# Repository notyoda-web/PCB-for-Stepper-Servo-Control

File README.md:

# STM32 Black Pill Stepper & Servo Control Board - Pin Mapping & Connections

This document details the exact pin-to-pin net connections and interface routing between the STM32 Black Pill microcontroller, the power subsystems, the A4988 stepper drivers, the servo headers, and communication peripherals, as established in the KiCad schematic .

---

## Power Input & Regulation Subsystem

* **J1 (XT60PW-M Power Input):**
  * Pin `P` (Positive / 12V rail): Connects directly to the main 3S LiPo battery input line, feeding the input terminals of both buck converters (`12V`) and the VMOT pins of A4988 drivers `A1` and `A2`.
  * Pin `N` (Negative / GND): Connects to the system common ground (`GND`).
* **3.3V Buck Converter:**
  * Input: Connected to `12V` rail from J1.
  * Output: Connected to the `3.3V` net, providing power to the Black Pill `VDD`/`3.3V` pins and auxiliary logic. Bulk smoothing capacitor `C1` is placed across the output.
* **5V Buck Converter:**
  * Input: Connected to `12V` rail from J1.
  * Output: Connected to the `5V` net, supplying power to the four hobby servo motor headers (`N1`, `N2`, `N5`, `N6`). Bulk smoothing capacitor `C2` is placed across the output.

---

# Power Distribution & Decoupling Rationale

This document outlines the engineering reasons for using dual buck converters and four electrolytic capacitors in the STM32 Black Pill stepper and servo control board, as shown in the schematic and PCB layout.

---

## 1. The Use of Two Buck Converters

The board utilizes two separate step-down (buck) converters fed by the 3S LiPo battery (`12V` net) to establish distinct power domains:

* **Isolation of Inductive Noise:** Stepper motors and hobby servos generate massive voltage transients, back-EMF, and high-frequency current spikes on their power rails during switching and stalling. By separating the regulation paths, noisy high-power actuator rails are prevented from coupling directly into sensitive digital logic.
* **Dedicated Voltage Domains:** 
  * **5V Buck Converter:** Powers the four hobby servos (`N1`, `N2`, `N5`, `N6`), which draw heavy peak currents under load. Supplying them from a dedicated regulator prevents voltage sags from resetting the microcontroller.
  * **3.3V Buck Converter:** Supplies a clean, stable regulated voltage exclusively to the Black Pill microcontroller (`VDD`/`3.3V`), protecting its internal ADC, core logic, and communication peripherals from brownouts.

---

## 2. The Use of Four Electrolytic Capacitors (`C1`, `C2`, `C3`, `C4`)

The four bulk electrolytic capacitors serve specific filtering and energy-storage functions across the power architecture:

* **Regulator Output Smoothing (`C1` and `C2`):**
  * **`C1` (3.3V Rail):** Placed at the output of the 3.3V buck converter to filter out residual switching ripple, ensuring a steady, low-noise supply for the Black Pill.
  * **`C2` (5V Rail):** Positioned at the 5V regulator output to provide bulk charge reservoirs that instantly compensate for current surges when servos suddenly start moving or change direction.
* **Motor Driver Local Decoupling (`C3` and `C4`):**
  * **`C3` and `C4` (VMOT Decoupling):** Connected directly across the motor supply (`VMOT`) and ground (`GND`) of the two A4988 driver modules (`A1` and `A2`). 
  * **Transient Suppression:** Stepper drivers rapidly chop high currents through inductive windings, creating high-frequency voltage spikes that can destroy silicon. These bulk capacitors act as local energy buffers right next to the driver chips, absorbing back-EMF spikes and stabilizing the input voltage during rapid microstepping steps.

## Stepper Motor Subsystem (A4988 Drivers & Connectors)

* **Driver A1 (Left Stepper Driver):**
  * **Power & Decoupling:** `VMOT` connected to `12V` with electrolytic decoupling capacitor `C3` tied to `GND`; `VDD` connected to `3.3V`.
  * **Control Pins:** 
    * `STEP` $\rightarrow$ Connected to MCU pin `PA1`.
    * `DIR` $\rightarrow$ Connected to MCU pin `PA2`.
    * `ENABLE` $\rightarrow$ Connected to MCU pin `PA6`.
    * Microstepping (`MS1`, `MS2`, `MS3`) $\rightarrow$ Tied to MCU pins `pb2`, `pb1`, `pb0` respectively.
    * `SLEEP` & `RESET` $\rightarrow$ Tied together on the module.
  * **Motor Output (`N4`):**
    * Pins `1B`, `1A`, `2A`, `2B` mapped directly from A1 driver pins 3, 4, 5, 6 to motor connector `N4` (`1A1_181`, `1A`, `2A`, `2B`).

* **Driver A2 (Right Stepper Driver):**
  * **Power & Decoupling:** `VMOT` connected to `12V` with electrolytic decoupling capacitor `C4` tied to `GND`[cite: 3]; `VDD` connected to `3.3V`.
  * **Control Pins:**
    * `STEP` $\rightarrow$ Connected to MCU pin `PB15`.
    * `DIR` $\rightarrow$ Connected to MCU pin `PB14`.
    * `ENABLE` $\rightarrow$ Connected to MCU pin `PB5`.
    * Microstepping (`MS1`, `MS2`, `MS3`) $\rightarrow$ Tied to MCU pins `pb14` (shared/routed), `pb13`, `pb12`.
    * `SLEEP` & `RESET` $\rightarrow$ Tied together on the module.
  * **Motor Output (`N3`):**
    * Pins `1B`, `1A`, `2A`, `2B` mapped directly from A2 driver pins to motor connector `N3`.

---

## Servo Motor Subsystem

All four servo headers share a common power (`5V`) and ground (`GND`) bus, with individual PWM control lines driven directly by MCU GPIO/timer pins:

* **Servo Header N2:** Pin 1 (Signal) $\rightarrow$ MCU pin `PB6`; Pin 2 $\rightarrow$ `5V`; Pin 3 $\rightarrow$ `GND`.
* **Servo Header N1:** Pin 1 (Signal) $\rightarrow$ MCU pin `PB7`; Pin 2 $\rightarrow$ `5V`; Pin 3 $\rightarrow$ `GND`.
* **Servo Header N6:** Pin 1 (Signal) $\rightarrow$ MCU pin `PB8`; Pin 2 $\rightarrow$ `5V`; Pin 3 $\rightarrow$ `GND`.
* **Servo Header N5:** Pin 1 (Signal) $\rightarrow$ MCU pin `PB9`; Pin 2 $\rightarrow$ `5V`; Pin 3 $\rightarrow$ `GND`.

---

## Communication Interface (UART)

* **J3 (UART Header):**
  * Pin 1 (`Rx`) $\rightarrow$ Connected to Black Pill MCU pin `PA9` (`Tx` of USART1) for host ingestion.
  * Pin 2 (`Tx`) $\rightarrow$ Connected to Black Pill MCU pin `PA10` (`Rx` of USART1) for telemetry transmission.
  * Pin 3 (`GND`) $\rightarrow$ Connected to system common ground (`GND`).

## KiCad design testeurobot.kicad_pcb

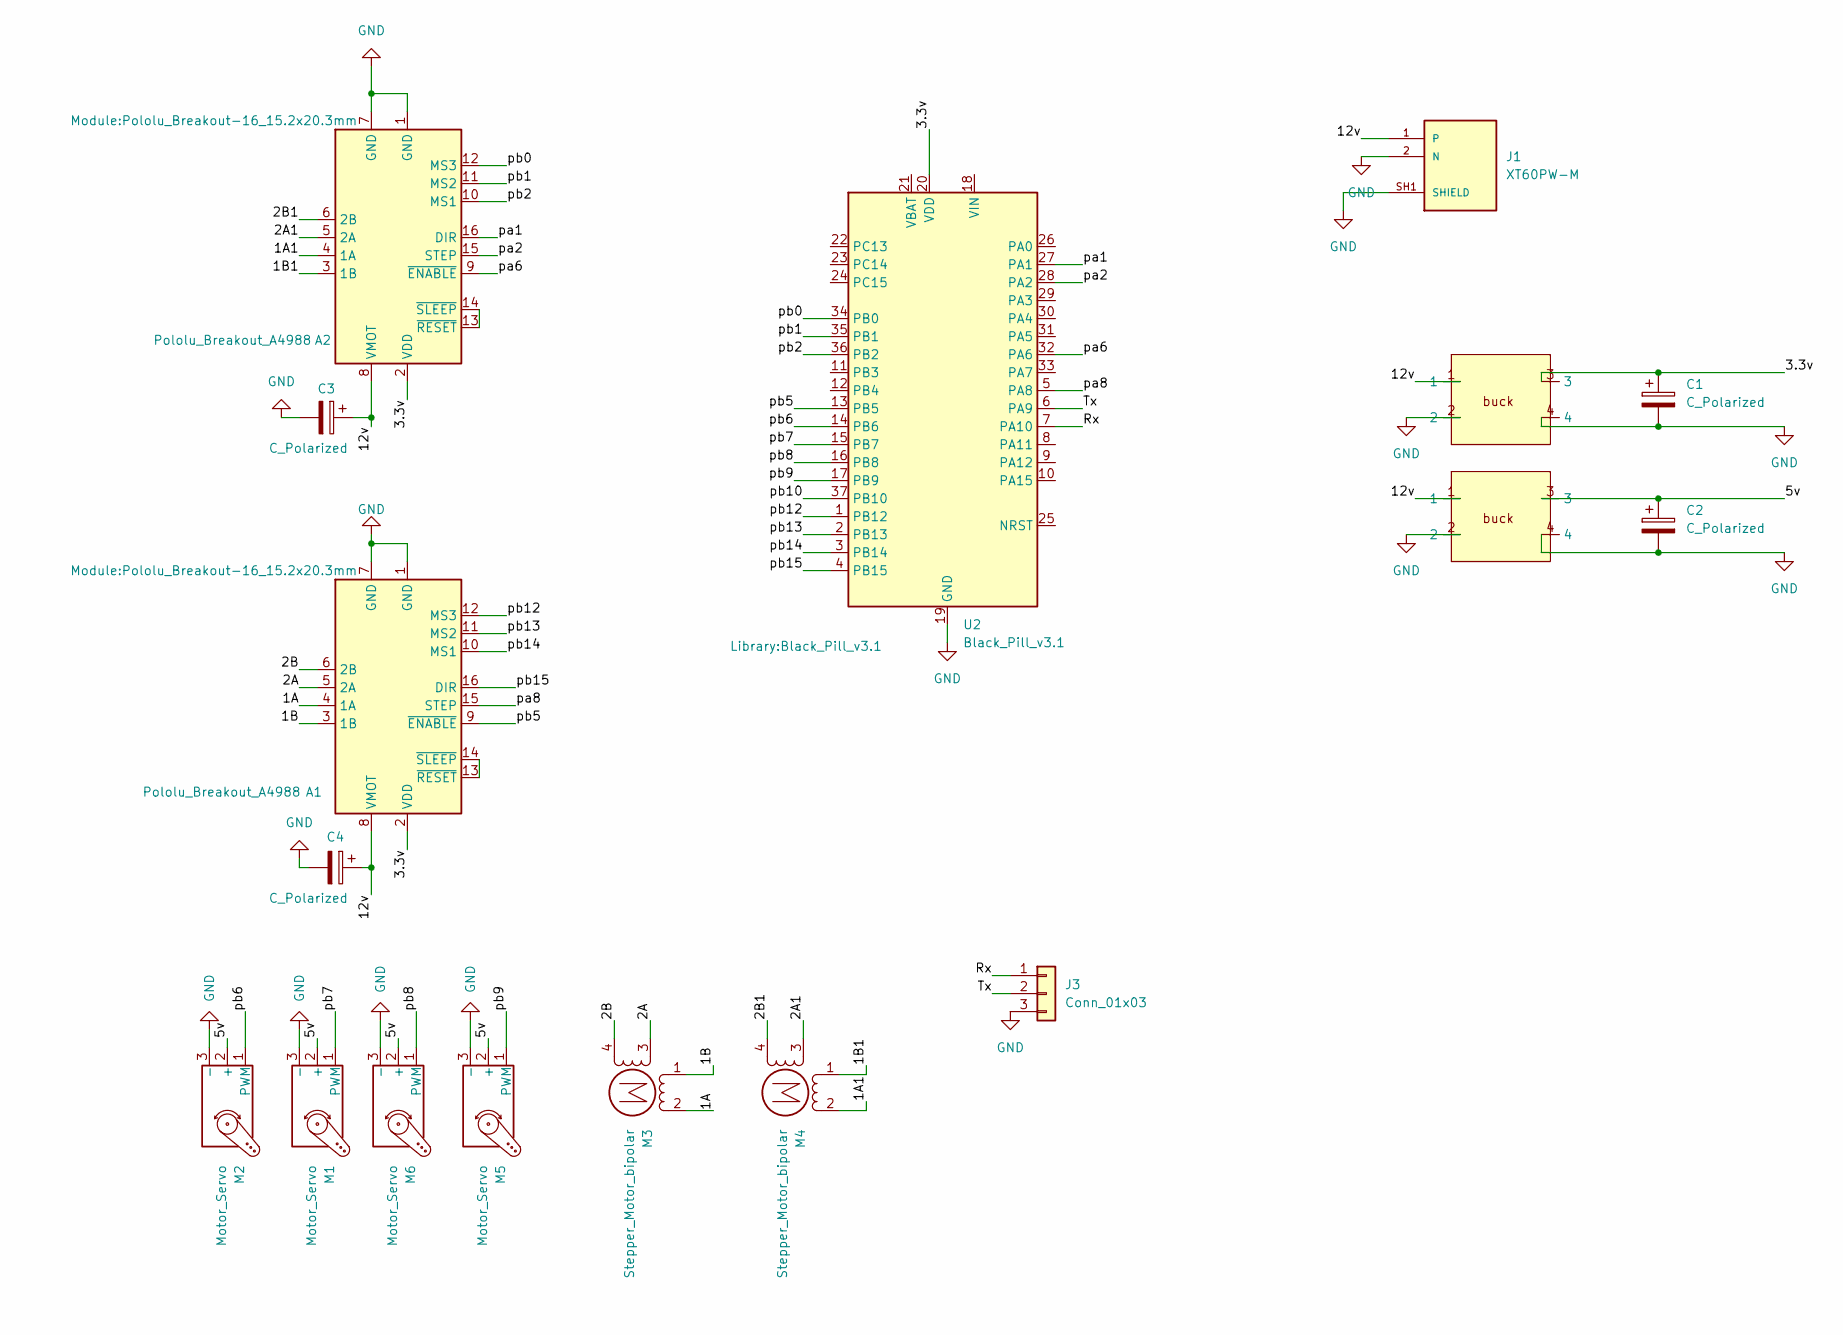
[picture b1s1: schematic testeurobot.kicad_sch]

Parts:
A1, A2: Pololu_Breakout_A4988; Pololu_Breakout-16_15.2x20.3mm
C1, C2, C3, C4: C_Polarized; CP_Radial_D7.5mm_P2.50mm
J1: XT60PW-M; AMASS_XT60PW-M; PARTREV 1.2
J3: Conn_01x03; PinHeader_1x03_P2.00mm_Vertical
M1, M2, M5, M6: Motor_Servo; PinHeader_1x03_P2.00mm_Vertical
M3, M4: Stepper_Motor_bipolar; PinHeader_1x04_P2.00mm_Vertical
U1, U3: buck
U2: Black_Pill_v3.1

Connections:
/1A: A1.4 (1A), M3.2 (-)
/1A1: A2.4 (1A), M4.2 (-)
/1B: A1.3 (1B), M3.1
/1B1: A2.3 (1B), M4.1
/2A: A1.5 (2A), M3.3
/2A1: A2.5 (2A), M4.3
/2B: A1.6 (2B), M3.4
/2B1: A2.6 (2B), M4.4
/5v: C2.1, M1.2 (+), M2.2 (+), M5.2 (+), M6.2 (+), U3.3
/12v: A1.8 (VMOT), A2.8 (VMOT), C3.1, C4.1, J1.1, U1.1, U3.1
/Rx: J3.1, U2.7 (PA10)
/Tx: J3.2, U2.6 (PA9)
/pa1: A2.16 (DIR), U2.27 (PA1)
/pa2: A2.15 (STEP), U2.28 (PA2)
/pa6: A2.9 (~ENABLE), U2.32 (PA6)
/pa8: A1.15 (STEP), U2.5 (PA8)
/pb0: A2.12 (MS3), U2.34 (PB0)
/pb1: A2.11 (MS2), U2.35 (PB1)
/pb2: A2.10 (MS1), U2.36 (PB2)
/pb5: A1.9 (~ENABLE), U2.13 (PB5)
/pb6: M2.1 (PWM), U2.14 (PB6)
/pb7: M1.1 (PWM), U2.15 (PB7)
/pb8: M6.1 (PWM), U2.16 (PB8)
/pb9: M5.1 (PWM), U2.17 (PB9)
/pb10: U2.37 (PB10)
/pb12: A1.12 (MS3), U2.1 (PB12)
/pb13: A1.11 (MS2), U2.2 (PB13)
/pb14: A1.10 (MS1), U2.3 (PB14)
/pb15: A1.16 (DIR), U2.4 (PB15)
GND: A1.1 (GND), A1.7 (GND), A2.1 (GND), A2.7 (GND), C1.2, C2.2, C3.2, C4.2, J1.2 (N), J1.SH1 (SHIELD), J1.SH2 (SHIELD), J3.3, M1.3 (-), M2.3 (-), M5.3 (-), M6.3 (-), U1.2, U1.4, U2.19 (GND), U2.39 (GND), U3.2, U3.4
unnamed: A1.13 (~RESET), A1.14 (~SLEEP)
unnamed: A2.13 (~RESET), A2.14 (~SLEEP)
VDD: A1.2 (VDD), A2.2 (VDD), C1.1, U1.3, U2.20 (VDD), U2.38 (VDD)
VIN: U2.18 (VIN), U2.40 (VIN)

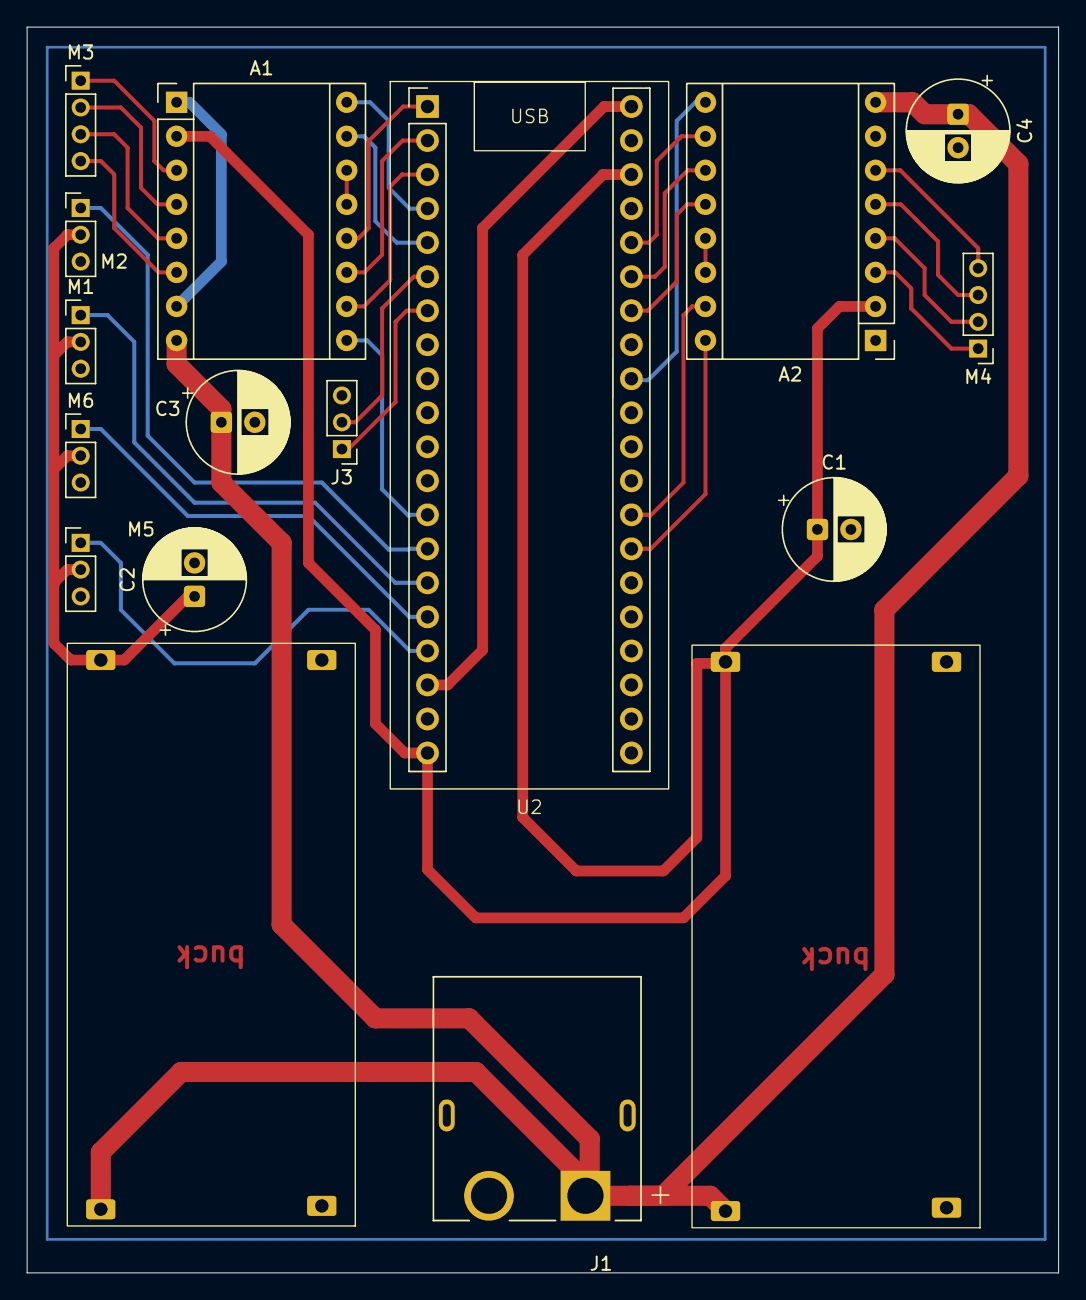
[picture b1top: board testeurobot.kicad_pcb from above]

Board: 2 copper layers, 77.0 x 93.0 mm, 17 parts (0 on the bottom side), 33 nets.
